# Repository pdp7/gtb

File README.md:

## "After Dark" Butterfly plus Getting to Blinky for Open Hardware Summit

* [Read the OSH Park blog post](https://blog.oshpark.com/2020/03/06/goodies-for-the-open-hardware-summit/)
* [The Open Hardware Summit is next week, March 13th, 2020](http://2020.oshwa.org/)
* [Everyone will receive one in their conference goodie bags](https://twitter.com/pdp7/status/1235885595332878336).
  * Thanks so much to Kevin Walseth at Digi-Key for making it happen! ⚡️ 
  * [Thanks to our Dan (@tekdemo) for the beautiful “After Dark” PCB art 🦋](https://twitter.com/pdp7/status/1235885597459443718)
  * [Thanks to Chris Gammell for the “Getting to Blinky” videos!](https://github.com/pdp7/gtb
) 🎥 It is a great way to learn KiCad!
  * [Thanks to Kyle at Digi-Key for showing what that board looks like in action!](https://twitter.com/KyletheDKgeek/status/1234891813112164353)
* I made the curved traces with the [“Rounder for Tracks” KiCad plugin from the RF-tools repo](https://github.com/easyw/RF-tools-KiCAD):
* the [design is also available an OSH Park shared project](https://oshpark.com/shared_projects/gasESAVc)
  * Note: after adding the board to the cart, please click on the “After Dark (Black Substrate + Clear Mask)” option

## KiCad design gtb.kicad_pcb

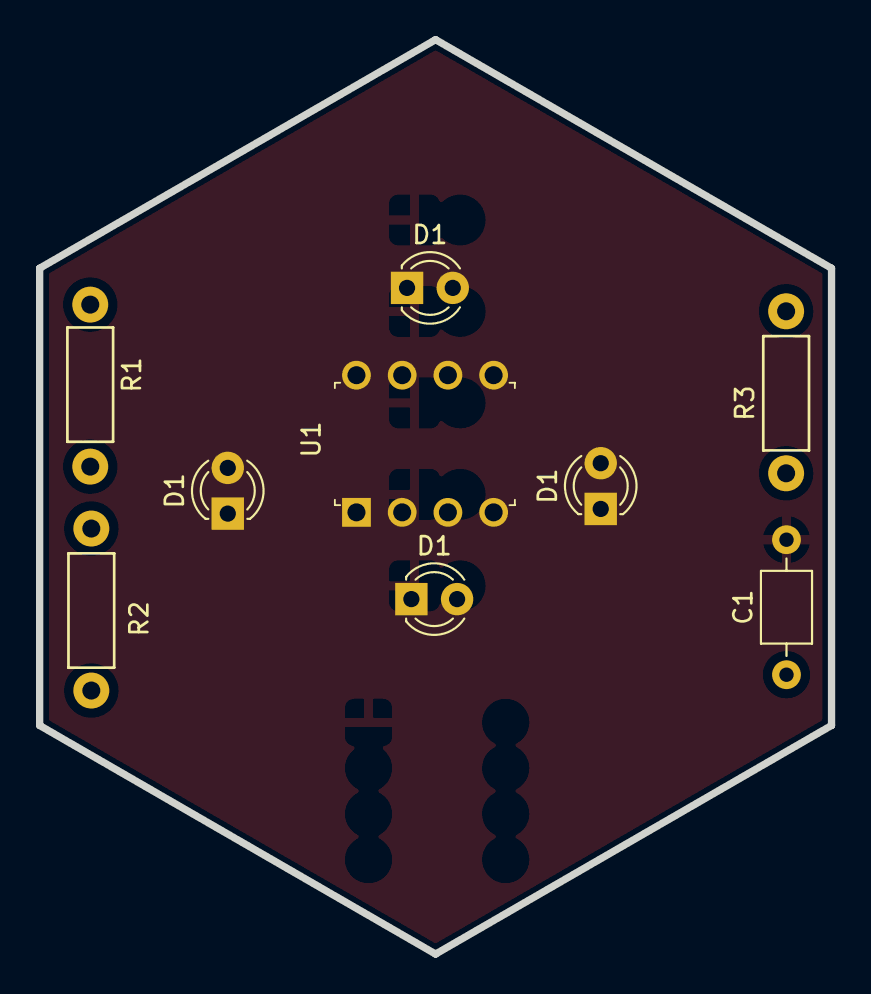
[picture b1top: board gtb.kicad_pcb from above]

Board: 6 copper layers, 44.0 x 50.8 mm, 10 parts (1 on the bottom side), 6 nets.

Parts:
C1: 1uF; C_Axial_L3.8mm_D2.6mm_P7.50mm_Horizontal
CR1220: BatteryHolder_Keystone_3000_1x12mm
D1, D1#2, D1#3, D1#4: LED; LED_D3.0mm
R1: 1K; RES-CARBONFILM-7MM
R2: 470K; RES-CARBONFILM-7MM
R3: 100; RES-CARBONFILM-7MM
U1: 7555; DIP-8_W7.62mm

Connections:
/VDD: CR1220.1, R1.1, U1.4, U1.8
GND: C1.2, CR1220.2, D1.1, D1#2.1, D1#3.1, D1#4.1, U1.1
unnamed: C1.1, R2.2, U1.2, U1.6
unnamed: D1.2, D1#2.2, D1#3.2, D1#4.2, R3.2
unnamed: R1.2, R2.1, U1.7
unnamed: R3.1, U1.3

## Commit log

2020-02-12 add files for Getting to Blinky
2020-02-12 add csv bom
2020-02-12 add digikey cart url
2020-02-12 flip to backside of board
2020-02-21 Add digikey cart for BoM
2020-03-06 add images
2020-03-06 add image
2020-10-25 add pumpkin
2021-01-20 update 6 layer version
2021-01-20 add no mask over tracks version
2021-01-20 update GTB designs
